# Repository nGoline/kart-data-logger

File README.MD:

# ESP32 Kart Telemetry System

A telemetry and datalogging system for open-track go-karts, built around a single
steering-wheel-mounted ESP32 display board that handles everything: GPS
acquisition, lap timing, dashboard rendering and SD logging.

> **Note:** earlier revisions of this project split the work between a
> helmet-mounted logger node and the display, linked over ESP-NOW. That helmet
> node proved unreliable at the track and has been removed — the display is now
> the only node.

## System Architecture

Single target: the **Display Dashboard Node**.

* **Board:** JC3248W535N (ESP32-S3, AXS15231B QSPI panel)
* **Role:** GPS acquisition, lap detection, UI dashboard, and SD logging.
* **Features:**
  * GPS from ATGM336 (default) or u-blox M9, wired directly to the board.
  * Live speed, G-force, satellite count and display battery state.
  * Finish-line based lap detection with best/previous lap deltas.
  * Telemetry logged to SD card per recording session.
  * Optional MPU6050 IMU for speed filtering and steering angle.

### Build targets in `platformio.ini`

Both targets build the same application (`src/main_display.cpp`) and differ only
in the panel driver backend:

* `env:display_gfx` — Arduino_GFX backend (`lib/DisplayGFX`). **Default.**
* `env:display` — esp_lcd backend (`lib/DisplayBSP`). Fallback.

The Arduino_GFX backend is the default because it resolves a QSPI panel wedge
seen with the esp_lcd path.

## Key Technical Features

* **Modular GPS provider** abstraction in `GpsManager`.
* **Finish-line lap detection** in `LapManager`, driven by GPS position.
* **`fix_stride.py` prebuild patch** for SquareLine Studio LVGL 9 image exports.
* **Display-wedge watchdog** — a 5s task watchdog on `loopTask` turns a panel
  wedge into a fast auto-reset instead of a permanent freeze.
* **Charge mode** to keep the board from eating the charger's current budget.
* **Optional IMU support** to improve speed filtering and live telemetry.

## Charge mode

The charger's current is shared between the board and the cell, so a running
dashboard slows charging considerably. Charge mode parks the device:

* Stops the recording session and closes the GPS UART.
* Drops the CPU to 80 MHz (the floor for stable USB-CDC — don't go lower).
* Swaps to a minimal charge screen and blanks the backlight after 15s.

It is **only ever entered manually**, from the `CHARGE MODE` button on the
config screen. Nothing enters it automatically, so bench testing and debugging
are unaffected.

While parked: tap anywhere to wake the backlight and read the battery for
another 15s; press `RESUME` to leave. Resuming re-probes the GPS, which takes a
couple of seconds.

> **Whether the GPS actually sleeps depends on which one is fitted.** Charge mode
> calls `gps.standby()` and leaves the UART open so `wake()` can talk to it.
> On the **ATGM336** that is a quiesce, not a sleep: the RF front end has no
> software power-down at all, so it keeps drawing ~25-40 mA and standby only cuts
> it to GPS-only at 1Hz with NMEA muted. On the **u-blox M9** it is a real
> power-down — `UBX-RXM-PMREQ` software backup, woken by traffic on the module's
> RX pin. Coming back may cost a cold start if the module's V_BCKP does not hold
> the BBR, but the configuration itself is in flash and survives either way.

> **The percentage reads high while charging.** With no power-path charger the
> sense divider sits on the charger rail, so it measures the cell terminal
> voltage *under charge*, which is well above its resting value — expect a
> jump downward when you unplug. It's shown as `~94%` to mark it approximate;
> the voltage below it is the number to trust.

The charge screen and the config-screen button are both built at runtime in
`lib/UiHelper/uiHelper.cpp` rather than exported from SquareLine, so
re-exporting `lib/ui/` will not wipe them.

## Hardware Requirements

* JC3248W535N display board
* GPS module wired to `RX=6` / `TX=7` — ATGM336, or a u-blox M9 such as the Matek
  M9N-5883. The ATGM336 runs on 3V3; the M9N-5883 wants 4~5.5V, so its VCC belongs
  on the IP5306 5V rail, not the board's 3V3.
* Optional MPU6050 IMU
* microSD card formatted FAT32

## Software Dependencies

Built with PlatformIO.

* `lvgl/lvgl` (v9.x)
* `moononournation/GFX Library for Arduino` (`display_gfx` only)
* `mikalhart/TinyGPSPlus`
* `ElectronicCats/MPU6050`

## GPS Providers

`GpsManager` supports two providers. Nothing older than these is supported — the
NEO-6M-era 9600-baud fallback is gone.

* **ATGM336 provider** (current default)
  * Enabled with `-D GPS_PROVIDER_ATGM336`.
  * 10Hz.
  * Configured over CASIC text commands (`$PCAS`), which are never acked, so the
    module cannot report whether a setting took. It also cannot be put to sleep:
    `$PCAS12` standby is a 5L-only feature and this is a 5N.
* **u-blox M9 provider** — targets the M9 generation (NEO-M9N), e.g. the Matek
  M9N-5883.
  * Leave `-D GPS_PROVIDER_ATGM336` out of the build flags.
  * 25Hz.
  * Probes 115200 then 38400 (the M9 default), and moves the port to 115200.
  * Sleeps for real in charge mode — `UBX-RXM-PMREQ` software backup, armed to
    wake on UART RX traffic.
  * Configured over binary UBX, which *is* acked, and the provider reads the
    dynamic model / rate / power mode back at boot and logs `BEFORE:` and
    `AFTER:` lines. Legacy `UBX-CFG-*` messages are deprecated on generation 9
    but still supported; they are removed on generation 10, so a future module
    means porting `configureUblox()` to `UBX-CFG-VALSET`.
  * **Speaks `UBX-NAV-PVT`, not NMEA.** All NMEA output is disabled. One 92-byte
    frame per epoch carries position at 1e-7° (~1.1cm), Doppler ground speed,
    UTC, `numSV`, `fixType`, `pDOP`, `hAcc` and `sAcc` — less traffic than
    GGA+RMC and strictly more information, as one coherent snapshot instead of a
    position from one sentence stitched to a speed from another. It also makes the
    four-constellation problem vanish: per-system duplication of GSA/GSV was an
    NMEA artefact, and UBX has no talker IDs to multiply.
  * `hasFix()` therefore uses the receiver's own verdict — `gnssFixOK`,
    `fixType == 3`, and `hAcc` within bounds — rather than the `sats >= 4 &&
    HDOP <= 3` heuristic the NMEA path had to guess with.
  * **TinyGPSPlus is unused on this path.** It stays in `lib_deps` for the
    ATGM336, and static-archive linking drops it (and the unreferenced provider)
    from the image. It is still compiled every build, so a break in either
    provider still fails the build.

The flag lives in `[display_common] -> build_flags_base`, so it applies to both
build targets at once.

### Fix rate

ATGM336 runs at **10Hz**, u-blox M9 at **25Hz** — the receiver's ceiling with all
four constellations. GGA+RMC at 25Hz is ~36kbaud of the 115200 the port is set to,
so the link has room to spare. 40ms epochs also land on exact centisecond values
(`.00`/`.04`/`.08`…), which matters because NMEA timestamps are centiseconds and
anything finer would round.

The rate buys **log resolution**, which is the point — at 100 km/h, 25Hz puts a
sample every 1.1m instead of every 2.8m. It buys much less for lap times, because
`LapManager` intersects the finish gate with the segment between consecutive fixes
and interpolates the crossing millisecond along it, so the reported time never
quantised to the fix interval in the first place.

To sustain 25Hz, `LogManager` holds the log file open for the whole session and
`flush()`es once a second, rather than reopening and closing it per row (25 FAT
directory updates a second is where a slow card starts stalling). The trade is
durability: an abrupt power-off now costs up to a second of the lap instead of a
single sample. The telemetry queue is 40 frames for the same reason — ~1.6s of
headroom at 25Hz, so a card stall doesn't drop rows.

### GPS wiring

The GPS UART pins are set by `GPS_STANDALONE_RX` / `GPS_STANDALONE_TX` in
`[display_common]`, currently `6` and `7`.

Watch for collisions when changing these: `GPIO5` carries the battery sense
divider (`DISPLAY_BATT_ADC` in `src/main_display.cpp`), and `GPIO18`/`GPIO17`
are the IMU's I2C pins when `ENABLE_IMU` is set.

## Session button

A momentary switch wired between `SESSION_BUTTON_PIN` and GND starts and stops
recording without touching the screen — the dash is on the steering wheel and the
touch target is small with gloves on.

* **Tap** — runs the same start gesture as the on-screen START button: the
  full-screen 3-2-1 overlay with the track name and a CANCEL, then the session
  begins (GoPro rolls, active track's finish line re-applied).
* **Hold 3 s** — stops it, counting `3 - 2 - 1` on the dashboard. Let go early and
  nothing happens.

The start overlay is parented to whatever screen is showing rather than to the
config screen, so it is visible when the physical button fires it from the
dashboard. Tapped from the config screen those are the same object, so the
on-screen button is unchanged.

The button is inert in charge mode — `loop()` returns before the display lock is
taken there, which is the point of that mode.

A tap while a session is already running does nothing: stopping is deliberately
the harder gesture, since an accidental stop costs the rest of the session.

Configured in `platformio.ini`:

| Flag | Default | Notes |
|---|---|---|
| `SESSION_BUTTON_PIN` | `6` | Comment out to build without a button |
| `SESSION_BUTTON_HOLD_MS` | `3000` | Hold time for the stop |
| `SESSION_BUTTON_ACTIVE_HIGH` | off | Set when the switch goes to 3V3 rather than GND |
| `SESSION_BUTTON_DEBOUNCE_MS` | `25` | Raise it if a long lead registers phantom taps |

Wire the switch between the pin and **GND** by default. If the spare wire in the
loom is a 3V3 instead, wire it pin-to-3V3 and set `SESSION_BUTTON_ACTIVE_HIGH` —
that swaps the internal pull-up for a pull-down, so the idle level is still the
released one. The pin is pulled to the idle rail either way and never left
floating: a floating input on a wire run out to a steering wheel picks up enough
to toggle on its own, and a broken wire then reads as *released* rather than as a
stuck press.

GPIO 6 is the ATGM336's old RX pad, already broken out and in the loom now that
the GPS is on 17/18. Other free pins: 7, 9, 10, 14, 15, 16, 41, 42. Avoid 0, 3,
45, 46 (strapping), 19/20 (native USB), 43/44 (UART0) and 26-37 (flash/PSRAM).

The state machine (`lib/SessionButton`) holds no GPIO or LVGL state, so it is
replayed on the host by `tools/lapreplay/sessionbutton.cpp` — bounce windows, a
release a millisecond short of the hold, and the `millis()` wrap, none of which
can be produced reliably with a thumb.

## Filesystem & Storage

The display reads and writes to a **FAT32 microSD** card. No files need to be
pre-populated — the display creates what it needs on first boot — but the files
below may be edited on a computer for configuration.

#### `/config.ini` (auto-created)

Stores display preferences. Created with defaults on first boot if absent.

```ini
# Kart Data Logger Configuration
theme=dark          # dark | light
selected_track=0    # index into tracks.ini
```

#### `/health.csv` (auto-created, only when something goes wrong)

Appended across every session, one row per second in which the telemetry queue
had no room for a frame:

```
epoch,log,dropped_total,dropped_delta
```

**An empty or absent file is the good news** — it means no row was ever lost. Any
row in it means the card could not keep up with the fix rate and the matching
`log_N.csv` is missing samples, so the file is worth checking after a race rather
than watching the serial log, which is unreachable with the dash on a wheel.

`epoch` comes from the GPS-synced system clock, so it lines up with the `epoch`
column in the telemetry file; before the first fix it degrades to uptime.

#### `/tracks.ini` (optional, user-created)

Defines named tracks with GPS finish-line coordinates. The display reads this at
boot and populates the track selector in the UI. If absent, no tracks are
preloaded.

```ini
# Kart track configurations
count=2

0_name=Kartódromo Granja Viana
0_left_lat=-23.60488969
0_left_lon=-46.83622658
0_right_lat=-23.60493793
0_right_lon=-46.83641597

1_name=My Track
1_left_lat=0.00000000
1_left_lon=0.00000000
1_right_lat=0.00000000
1_right_lon=0.00000000
```

#### `/log_N.csv` (auto-created per session)

Telemetry session logs. A new numbered file is created each time a recording
session starts.

```
epoch,speed,totalGForce,gForceX,gForceY,steering_angle,sats,lat,lng,fix,pdop,hacc,sacc
```

The last four are the receiver's report on its own fix, and are **zero on the
ATGM336** — NMEA carries no equivalent, so zero means "not reported", not "perfect".

| column | meaning |
| --- | --- |
| `fix`  | `0` no fix, `2` 2D, `3` 3D, `5` time only. Never `1`/`4` (dead reckoning) — that is NEO-M9V silicon, not M9N. |
| `pdop` | position dilution of precision |
| `hacc` | horizontal accuracy estimate, metres, ~1σ |
| `sacc` | speed accuracy estimate, m/s |

`hacc` is the useful one for analysis: it does not make a position better, it tells
you which samples to distrust. Around 0.7-1.5m under open sky, climbing near
buildings and in the first seconds after a cold start. A lap time interpolated
between two 12m samples is not a lap time to trust to hundredths.

These columns are **appended**, never inserted, so everything in `tools/` keeps
working — those read by column name or by a fixed `sscanf` prefix. A CSV derived
from GoPro footage simply lacks them.

Note `lat`/`lng` are written at 7 decimal places (~1.1cm) rather than 6 (~11cm),
which is what `UBX-NAV-PVT` actually resolves.

## Setup & Installation

1. Clone this repository.
2. Open it in VSCode with PlatformIO.
3. Edit the UI using the SquareLine Studio project files in `UIDesign/`.
4. Export the UI to `/lib/ui/` and let `fix_stride.py` patch LVGL image metadata during build.
5. Flash the firmware: `tools/flash.sh` (see below).
6. Insert a FAT32 microSD card into the display. A default `config.ini` is created on first boot.

### Flashing

`upload_port` in `platformio.ini` is pinned to `/dev/cu.usbmodem1101`, which is one
machine's enumeration — the same board comes up under a different name elsewhere and
`pio run -t upload` then fails on a port that isn't there. `tools/flash.sh` finds the
board by USB `VID:PID` instead and passes it with `--upload-port`, which overrides the
pinned value:

```bash
tools/flash.sh              # default env, confirm, then upload
tools/flash.sh -m           # ...and open the serial monitor afterwards
tools/flash.sh -e display   # the esp_lcd fallback env
tools/flash.sh -p /dev/cu.usbmodem101   # skip discovery
tools/flash.sh -y           # no confirmation prompt (also FLASH_YES=1)
tools/flash.sh -- -v        # anything after -- goes to `pio run`
```

Before uploading it prints the port, env and `FW_VERSION`, and warns if the tree is
dirty — `FW_VERSION` is `git describe --tags --always --dirty` and shows on the setup
screen, so it is easy to flash uncommitted edits by accident. If more than one board is
attached it lists the candidates and asks for `-p`.

`pio run -e display_gfx -t upload` still works if the pinned port happens to be right.

## Dormant libraries

These libraries are no longer part of the build — nothing includes them — but
they are kept in `lib/` because they may be useful again:

* `EspNowManager` + `Shared/EspNowProtocol.h` message types — the board-to-board radio link.
* `ErrorLogManager` — LittleFS error capture and transfer.
* `AudioManager`, `VoiceParser` — I2S playback and spoken number/lap announcements.
* `PowerManager` — button-driven hibernate and power gating.
* `FakeGps` — CSV replay for development without GPS hardware.

`Shared/EspNowProtocol.h` is still compiled: `TelemetryMsg` is the record the
display passes between the UI, the lap manager and the SD log task.

## Design files

Design files are included under the `hardware/` folder.

### 3D Models

I've used Fusion to design 3D models for the custom enclosures and mounts. These
are located in `hardware/3d-models/` and exported as `.f3d` and `.3mf` files.
You can open and modify these in Fusion or any compatible 3D modeling software.

## Visual Reference

The repository includes module photos in the `images/` folder.

## Notes

* The display firmware owns the whole pipeline: GPS, lap timing, UI and SD logging.
* Lap detection only runs while a recording session is active.

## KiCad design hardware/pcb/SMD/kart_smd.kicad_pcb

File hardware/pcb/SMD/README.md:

# SMD PCB Version

This folder contains the surface-mount board design files for the kart telemetry project.

Available files:

* `kart_smd.kicad_pcb` — SMD PCB layout.
* `kart_smd.kicad_sch` — schematic for the SMD board.
* `.history/` — KiCad project history and backups.

Use this variant when you want a compact, production-ready board with surface-mounted components.

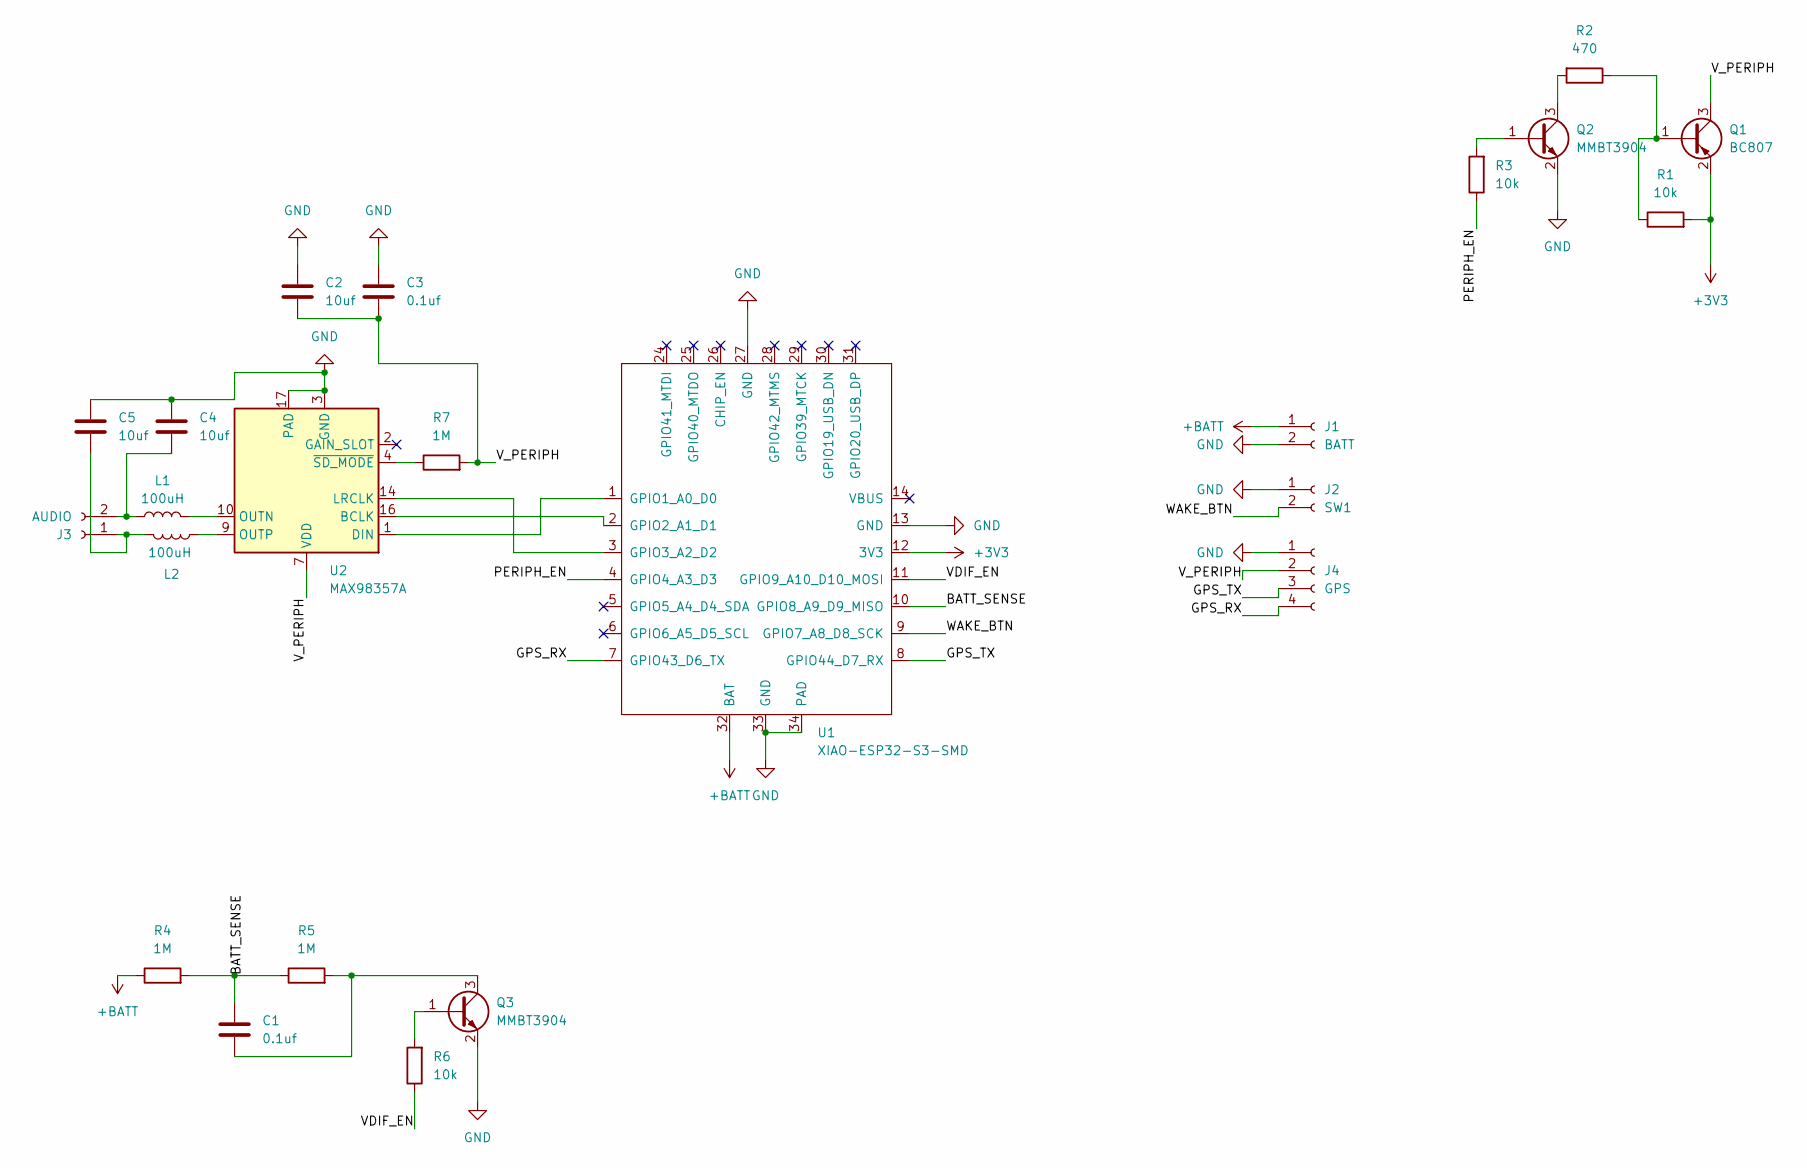
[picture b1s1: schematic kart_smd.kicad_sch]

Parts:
C1, C3: 0.1uf; C_0805_2012Metric
C2, C4, C5: 10uf; C_0805_2012Metric
J1: BATT; JST_PH_S2B-PH-K_1x02_P2.00mm_Horizontal
J2: SW1; JST_PH_S2B-PH-K_1x02_P2.00mm_Horizontal
J3: AUDIO; JST_PH_S2B-PH-K_1x02_P2.00mm_Horizontal
J4: GPS; JST_PH_S4B-PH-K_1x04_P2.00mm_Horizontal
L1, L2: 100uH; L_0805_2012Metric
Q1: BC807; SOT-23
Q2, Q3: MMBT3904; SOT-23
R1, R3, R6: 10k; R_0805_2012Metric
R2: 470; R_0805_2012Metric
R4, R5, R7: 1M; R_0805_2012Metric
U1: XIAO-ESP32-S3-SMD
U2: MAX98357A; TQFN-16-1EP_3x3mm_P0.5mm_EP1.23x1.23mm_ThermalVias

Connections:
+3V3: Q1.2 (E), R1.2, U1.12 (3V3)
+BATT: J1.1, R4.1, U1.32 (BAT)
/BATT_SENSE: C1.2, R4.2, R5.1, U1.10 (GPIO8_A9_D9_MISO)
/GPS_RX: J4.4, U1.7 (GPIO43_D6_TX)
/GPS_TX: J4.3, U1.8 (GPIO44_D7_RX)
/PERIPH_EN: R3.1, U1.4 (GPIO4_A3_D3)
/VDIF_EN: R6.1, U1.11 (GPIO9_A10_D10_MOSI)
/V_PERIPH: C2.2, C3.2, J4.2, Q1.3 (C), R7.2, U2.7 (VDD), U2.8 (VDD)
/WAKE_BTN: J2.2, U1.9 (GPIO7_A8_D8_SCK)
GND: C2.1, C3.1, C4.1, C5.1, J1.2, J2.1, J4.1, Q2.2 (E), Q3.2 (E), U1.13 (GND), U1.27 (GND), U1.33 (GND), U1.34 (PAD), U2.3 (GND), U2.11 (GND), U2.15 (GND), U2.17 (PAD)
unnamed: C5.2, J3.1, L2.2
unnamed: C4.2, J3.2, L1.1
unnamed: Q1.1 (B), R1.1, R2.1
unnamed: Q2.1 (B), R3.2
unnamed: Q2.3 (C), R2.2
unnamed: Q3.1 (B), R6.2
unnamed: C1.1, Q3.3 (C), R5.2
unnamed: U1.1 (GPIO1_A0_D0), U2.1 (DIN)
unnamed: U1.2 (GPIO2_A1_D1), U2.16 (BCLK)
unnamed: U1.3 (GPIO3_A2_D2), U2.14 (LRCLK)
unnamed: L1.2, U2.10 (OUTN)
unnamed: L2.1, U2.9 (OUTP)
unnamed: R7.1, U2.4 (~SD_MODE)

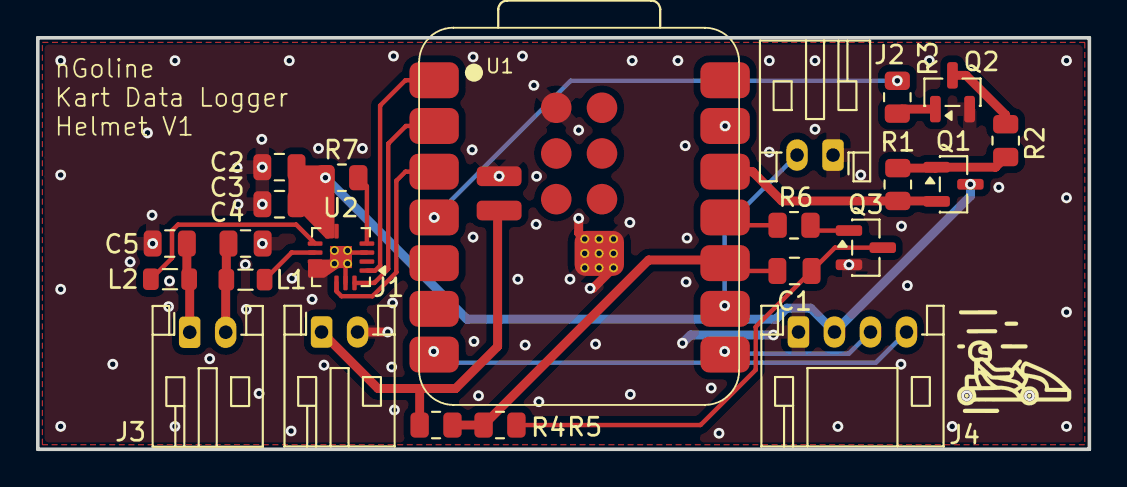
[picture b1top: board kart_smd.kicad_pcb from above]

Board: 2 copper layers, 58.4 x 22.9 mm, 23 parts (0 on the bottom side), 23 nets.

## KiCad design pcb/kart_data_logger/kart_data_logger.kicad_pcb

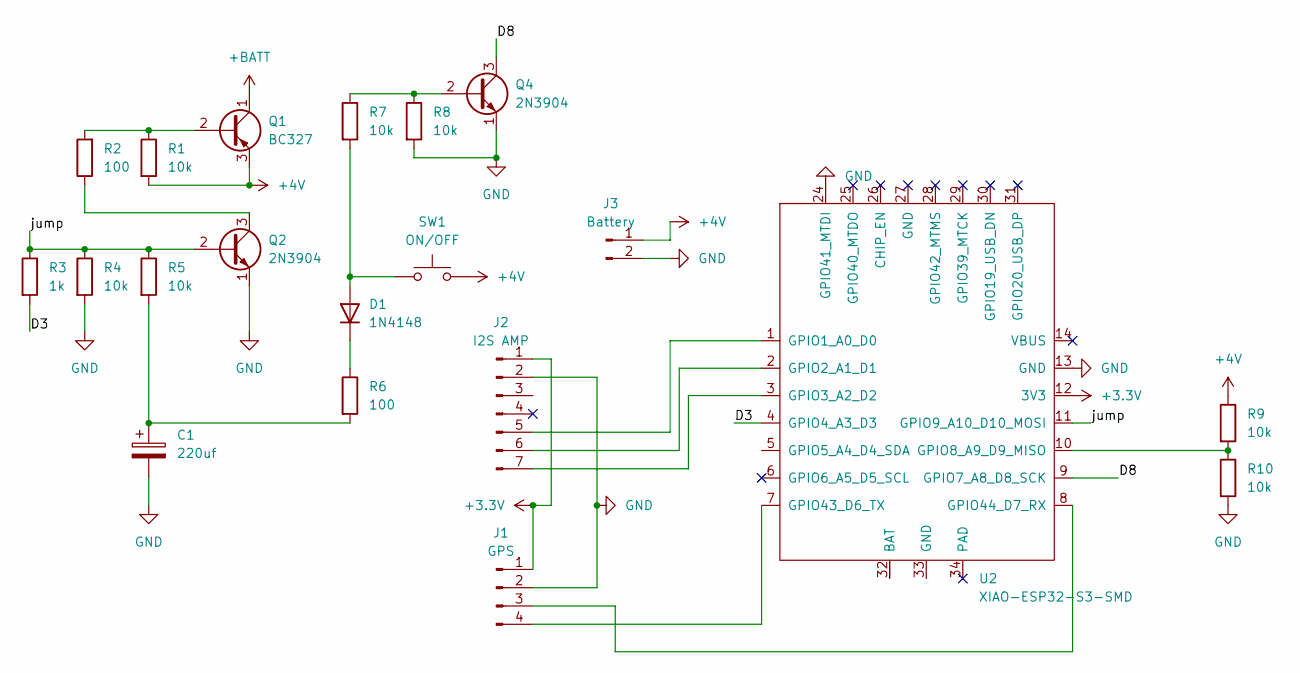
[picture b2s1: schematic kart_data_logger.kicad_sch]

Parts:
C1: 220uf; CP_Radial_D6.3mm_P2.50mm
D1: 1N4148; D_DO-34_SOD68_P7.62mm_Horizontal
J1: GPS; PinHeader_1x04_P2.54mm_Vertical
J2: I2S AMP; PinHeader_1x07_P2.54mm_Vertical
J3: Battery; PinHeader_1x02_P2.54mm_Vertical
Q1: BC327; TO-92_Inline_Wide
Q2, Q4: 2N3904; TO-92_Inline_Wide
R1, R4, R5, R7, R8, R9, R10: 10k; R_Axial_DIN0207_L6.3mm_D2.5mm_P7.62mm_Horizontal
R2, R6: 100; R_Axial_DIN0207_L6.3mm_D2.5mm_P7.62mm_Horizontal
R3: 1k; R_Axial_DIN0207_L6.3mm_D2.5mm_P7.62mm_Horizontal
SW1: ON/OFF; PinHeader_1x02_P2.54mm_Vertical
U2: XIAO-ESP32-S3-SMD

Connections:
+3.3V: J1.1, J2.1, U2.12 (3V3)
+4V: J3.1, Q1.3 (E), R1.2, R9.1, SW1.2
+BATT: Q1.1 (C)
/D3: R3.2, U2.4 (GPIO4_A3_D3)
/D8: Q4.3 (C), U2.9 (GPIO7_A8_D8_SCK)
/jump: Q2.2 (B), R3.1, R4.1, R5.1, U2.11 (GPIO9_A10_D10_MOSI)
GND: C1.2, J1.2, J2.2, J3.2, Q2.1 (E), Q4.1 (E), R4.2, R8.2, R10.2, U2.13 (GND), U2.24 (GPIO41_MTDI)
unnamed: C1.1, R5.2, R6.2
unnamed: D1.2 (A), R7.2, SW1.1
unnamed: D1.1 (K), R6.1
unnamed: J1.3, U2.8 (GPIO44_D7_RX)
unnamed: J1.4, U2.7 (GPIO43_D6_TX)
unnamed: J2.5, U2.1 (GPIO1_A0_D0)
unnamed: J2.6, U2.2 (GPIO2_A1_D1)
unnamed: J2.7, U2.3 (GPIO3_A2_D2)
unnamed: Q1.2 (B), R1.1, R2.2
unnamed: Q2.3 (C), R2.1
unnamed: Q4.2 (B), R7.1, R8.1
unnamed: R9.2, R10.1, U2.10 (GPIO8_A9_D9_MISO)

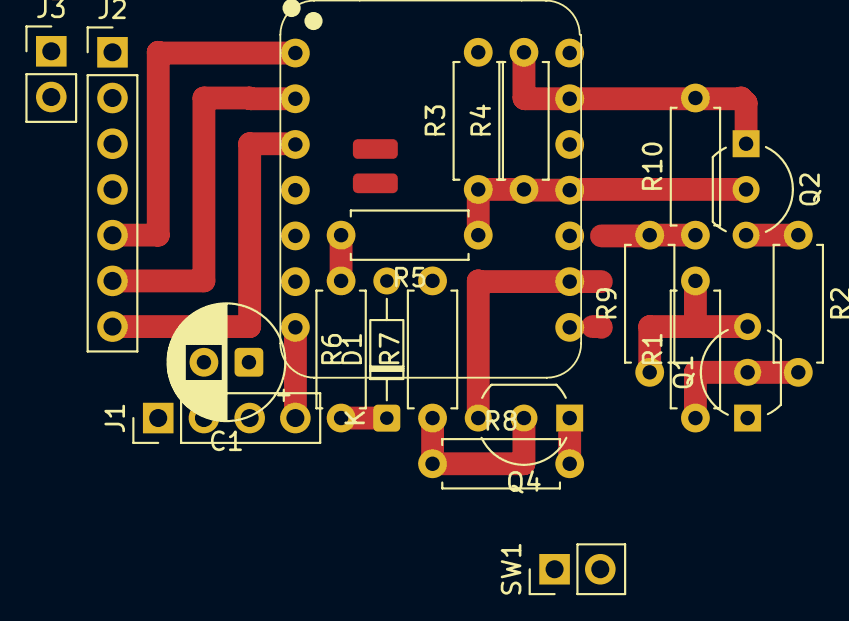
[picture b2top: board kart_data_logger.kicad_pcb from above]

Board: 12 copper layers, 20 parts (0 on the bottom side), 18 nets.

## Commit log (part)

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2026-03-02 add gps and imu
2026-03-02 add audio cue and clean-up the project
2026-03-02 add gps speed filter and download endpoint
2026-03-04 move logic to modules - i2c don't work with 12s
2026-03-05 fix i2c vs i2s race condition; add more visual cues to the display;
2026-03-05 add license and readme
2026-03-05 add helmet battery to display
2026-03-05 fix ublox startup code; update audio cues; refactor LapManager to for delta against last; add delta time to voice parser;
2026-03-06 update speed filter to get rid of false zeroes
2026-03-06 make esp-now logic more reliable; add debug logs; add logs to VoiceParser; fix AudioManager mutex;
2026-03-09 update LapManager to use a line gate instead of a radius gate; add g force meter to display; limit battery to 99% on display.
2026-03-21 add support to atgm336 gps+baidou module; add support for a latch circuit to turn on/off; add support for battery level cutt-off using the latch;
2026-03-24 updated KiCad project files; updated platformio.ini to change upload port and include MPU6050 library for IMU support; modified main_display.cpp to integrate IMU data handling and adjust telemetry ba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
2026-03-25 added ErrorLogManager class for managing error logs in LittleFS; introduced LoggingUtils.h for convenient logging macros; enhanced EspNowManager to handle error log transmission and acknowledgments; 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
2026-03-27 add date to log file
2026-03-31 software version 1 used on a real kart on 2026/03/26
2026-05-21 added new display board; removed esp32_smartdisplay in favor of local lib
2026-05-22 Replace the UI with a usable one.
2026-05-22 add ConfigManager to persist configurations and implement Theme selection
2026-05-22 add track setup screen
2026-05-22 Add on-demand session start/stop.
2026-05-22 add new message to exchange track information with the helmet
2026-05-22 move lap brain to display and enable display to work with gps (no helmet)
